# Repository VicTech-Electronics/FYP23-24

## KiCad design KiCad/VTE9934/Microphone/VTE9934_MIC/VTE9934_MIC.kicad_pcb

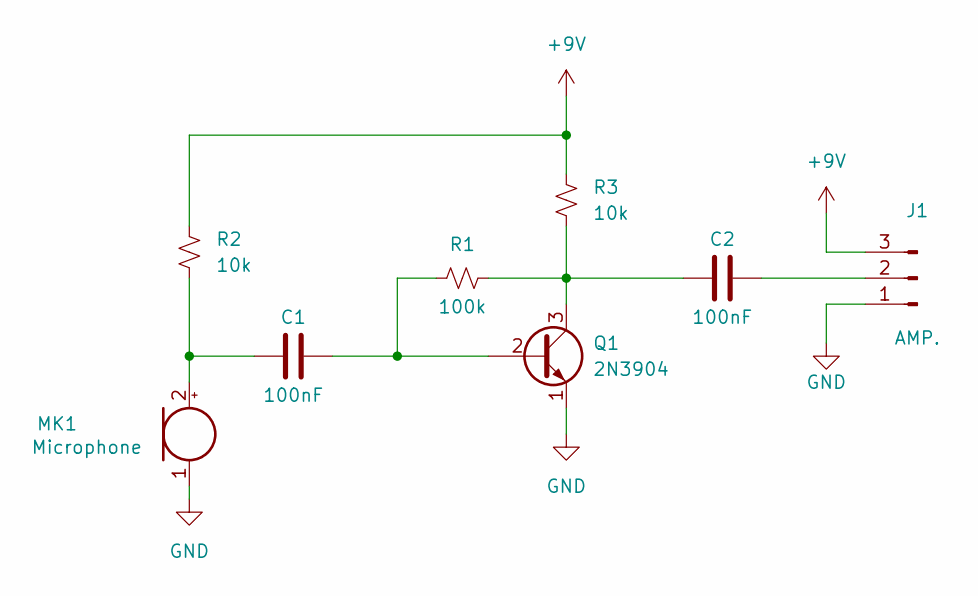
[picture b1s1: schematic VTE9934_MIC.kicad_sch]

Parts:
C1, C2: 100nF; C_Disc_D3.8mm_W2.6mm_P2.50mm
J1: AMP.; PinHeader_1x03_P2.54mm_Horizontal
MK1: Microphone; POM-2244P-C3310-2-R
Q1: 2N3904; TO-92_Inline
R1: 100k; R_Axial_DIN0207_L6.3mm_D2.5mm_P10.16mm_Horizontal
R2, R3: 10k; R_Axial_DIN0207_L6.3mm_D2.5mm_P10.16mm_Horizontal

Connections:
+9V: J1.3, R2.2, R3.2
GND: J1.1, MK1.1 (-), Q1.1 (E)
unnamed: C2.2, J1.2
unnamed: C1.1, MK1.2 (+), R2.1
unnamed: C1.2, Q1.2 (B), R1.1
unnamed: C2.1, Q1.3 (C), R1.2, R3.1

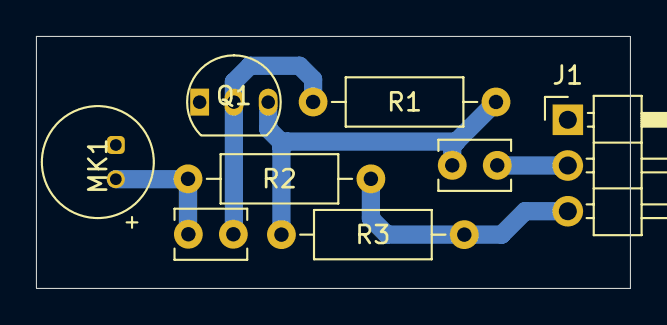
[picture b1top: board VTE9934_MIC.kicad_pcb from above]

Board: 2 copper layers, 33.0 x 14.0 mm, 8 parts (0 on the bottom side), 6 nets.

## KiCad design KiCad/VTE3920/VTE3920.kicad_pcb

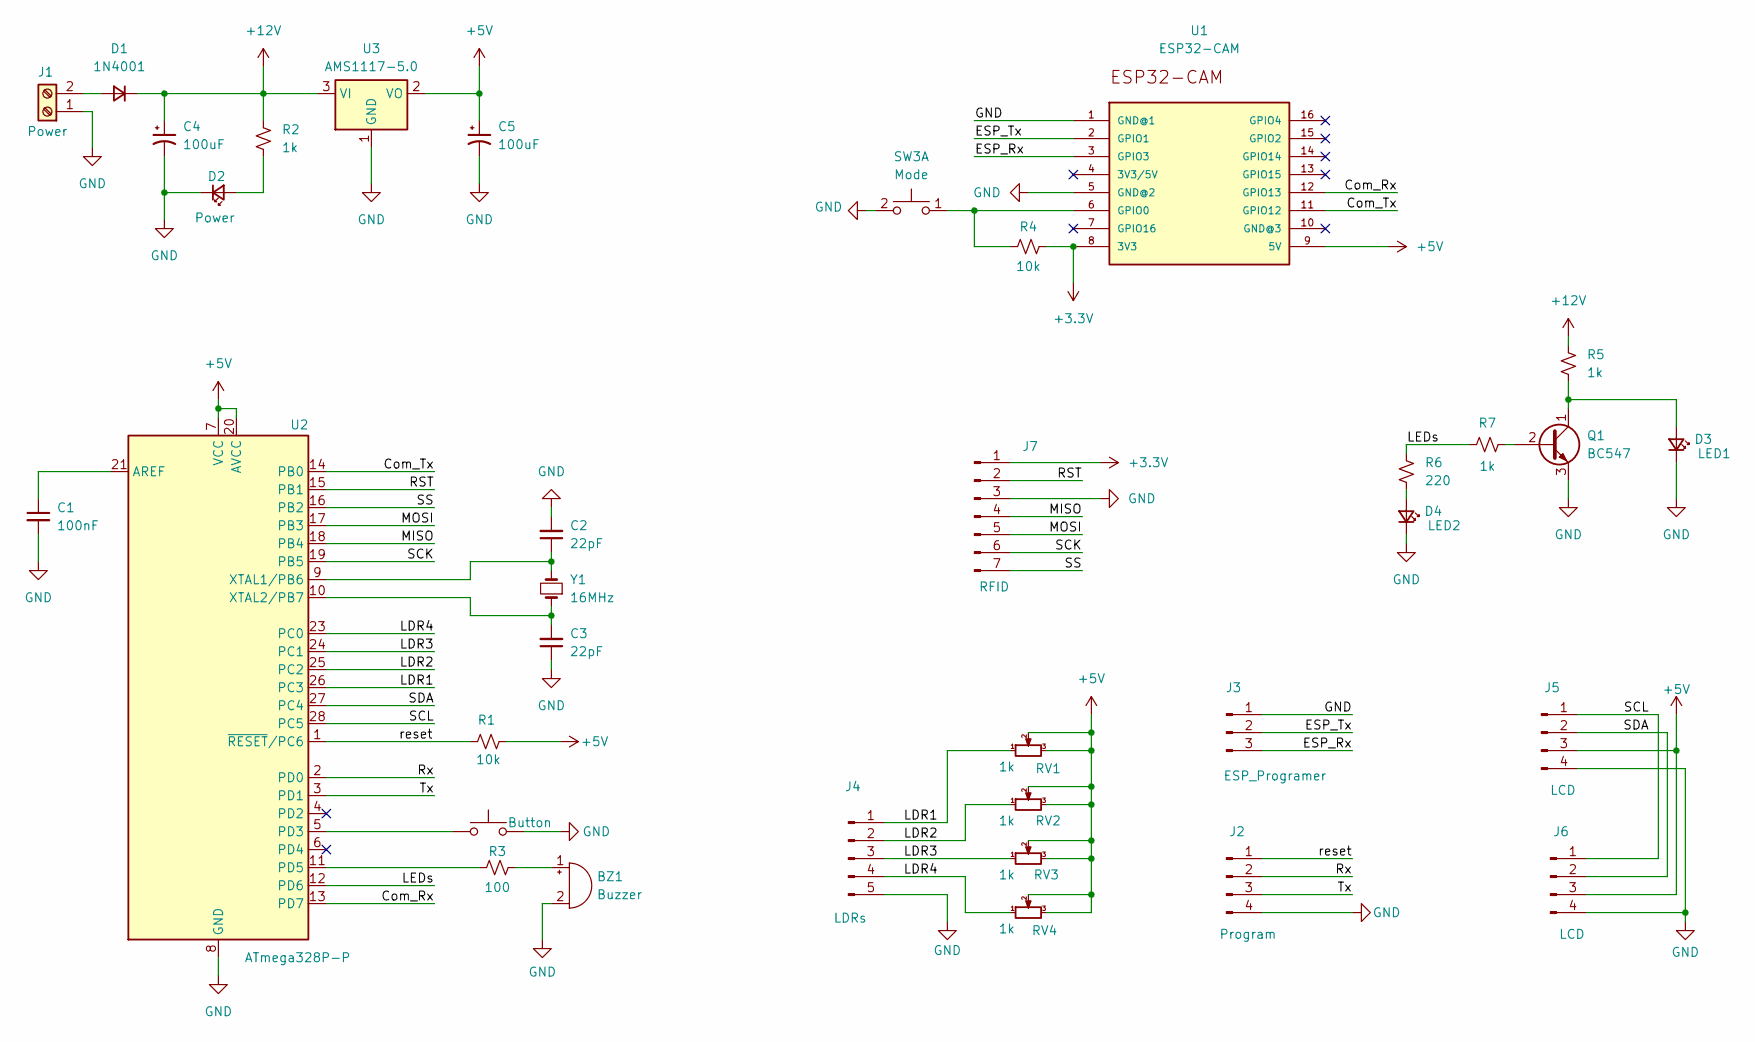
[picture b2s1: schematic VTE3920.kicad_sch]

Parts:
BZ1: Buzzer; Buzzer_12x9.5RM7.6
C1: 100nF; C_Disc_D3.0mm_W1.6mm_P2.50mm
C2, C3: 22pF; C_Disc_D3.0mm_W1.6mm_P2.50mm
C4, C5: 100uF; CP_Radial_D5.0mm_P2.50mm
D1: 1N4001; D_A-405_P10.16mm_Horizontal
D2: Power; LED_D3.0mm
D3: LED1; LED_D3.0mm
D4: LED2; LED_D3.0mm
J1: Power; TerminalBlock_bornier-2_P5.08mm
J2: Program; PinHeader_1x04_P2.54mm_Vertical
J3: ESP_Programer; PinHeader_1x03_P2.54mm_Vertical
J4: LDRs; PinHeader_1x05_P2.54mm_Vertical
J5, J6: LCD; PinHeader_1x04_P2.54mm_Vertical
J7: RFID; PinHeader_1x07_P2.54mm_Vertical
Q1: BC547; TO-92_Inline
R1, R4: 10k; R_Axial_DIN0207_L6.3mm_D2.5mm_P10.16mm_Horizontal
R2, R5, R7: 1k; R_Axial_DIN0207_L6.3mm_D2.5mm_P10.16mm_Horizontal
R3: 100; R_Axial_DIN0207_L6.3mm_D2.5mm_P10.16mm_Horizontal
R6: 220; R_Axial_DIN0207_L6.3mm_D2.5mm_P10.16mm_Horizontal
RV1, RV2, RV3, RV4: 1k; Potentiometer_Runtron_RM-065_Vertical
SW1: Button; TestPoint_2Pads_Pitch2.54mm_Drill0.8mm
SW3: Mode; SW_PUSH_6mm
U1: ESP32-CAM
U2: ATmega328P-P; DIP-28_W7.62mm_Socket_LongPads
U3: AMS1117-5.0; SOT-223-3_TabPin2
Y1: 16MHz; Crystal_HC50_Vertical

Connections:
+3.3V: J7.1, R4.2, U1.8 (3V3)
+5V: C5.1, J5.3, J6.3, R1.2, RV1.2, RV1.3, RV2.2, RV2.3, RV3.2, RV3.3, RV4.2, RV4.3, U1.9 (5V), U2.7 (VCC), U2.20 (AVCC), U3.2 (VO)
+12V: C4.1, D1.1 (K), R2.1, R5.1, U3.3 (VI)
/Com_Rx: U1.12 (GPIO13), U2.13 (PD7)
/Com_Tx: U1.11 (GPIO12), U2.14 (PB0)
/ESP_Rx: J3.3, U1.3 (GPIO3)
/ESP_Tx: J3.2, U1.2 (GPIO1)
/LDR1: J4.1, RV1.1, U2.26 (PC3)
/LDR2: J4.2, RV2.1, U2.25 (PC2)
/LDR3: J4.3, RV3.1, U2.24 (PC1)
/LDR4: J4.4, RV4.1, U2.23 (PC0)
/LEDs: R6.1, R7.1, U2.12 (PD6)
/MISO: J7.4, U2.18 (PB4)
/MOSI: J7.5, U2.17 (PB3)
/RST: J7.2, U2.15 (PB1)
/Rx: J2.2, U2.2 (PD0)
/SCK: J7.6, U2.19 (PB5)
/SCL: J5.1, J6.1, U2.28 (PC5)
/SDA: J5.2, J6.2, U2.27 (PC4)
/SS: J7.7, U2.16 (PB2)
/Tx: J2.3, U2.3 (PD1)
/reset: J2.1, R1.1, U2.1 (~RESET/PC6)
GND: BZ1.2 (-), C1.2, C2.2, C3.1, C4.2, C5.2, D2.1 (K), D3.1 (K), D4.1 (K), J1.1, J2.4, J3.1, J4.5, J5.4, J6.4, J7.3, Q1.3 (E), SW1.2, SW3.2 (D), U1.1 (GND@1), U1.5 (GND@2), U2.8 (GND), U2.22 (GND), U3.1 (GND)
unnamed: BZ1.1 (+), R3.2
unnamed: D1.2 (A), J1.2
unnamed: D2.2 (A), R2.2
unnamed: D3.2 (A), Q1.1 (C), R5.2
unnamed: D4.2 (A), R6.2
unnamed: Q1.2 (B), R7.2
unnamed: R4.1, SW3.1 (C), U1.6 (GPIO0)
unnamed: C1.1, U2.21 (AREF)
unnamed: SW1.1, U2.5 (PD3)
unnamed: R3.1, U2.11 (PD5)
unnamed: C2.1, U2.9 (XTAL1/PB6), Y1.2
unnamed: C3.2, U2.10 (XTAL2/PB7), Y1.1

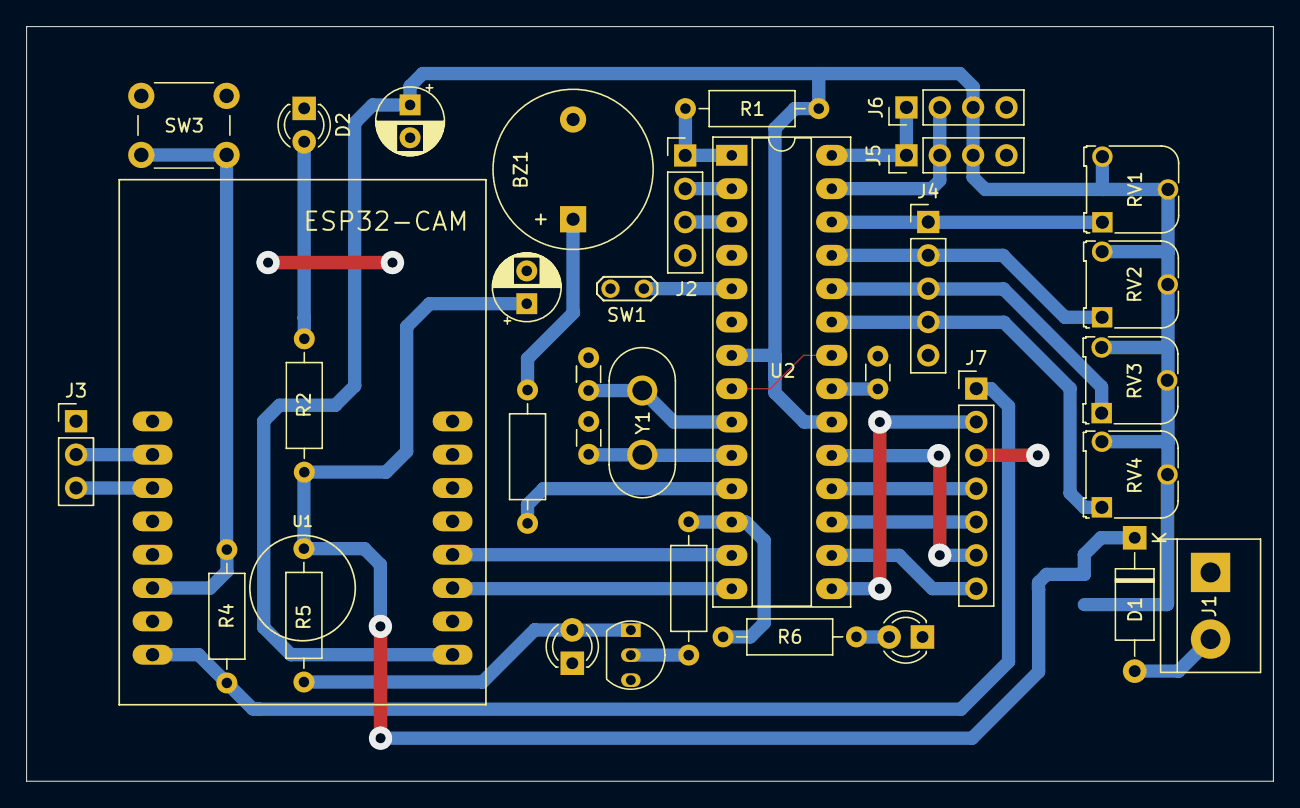
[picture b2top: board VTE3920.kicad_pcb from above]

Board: 2 copper layers, 95.0 x 57.5 mm, 35 parts (1 on the bottom side), 35 nets.

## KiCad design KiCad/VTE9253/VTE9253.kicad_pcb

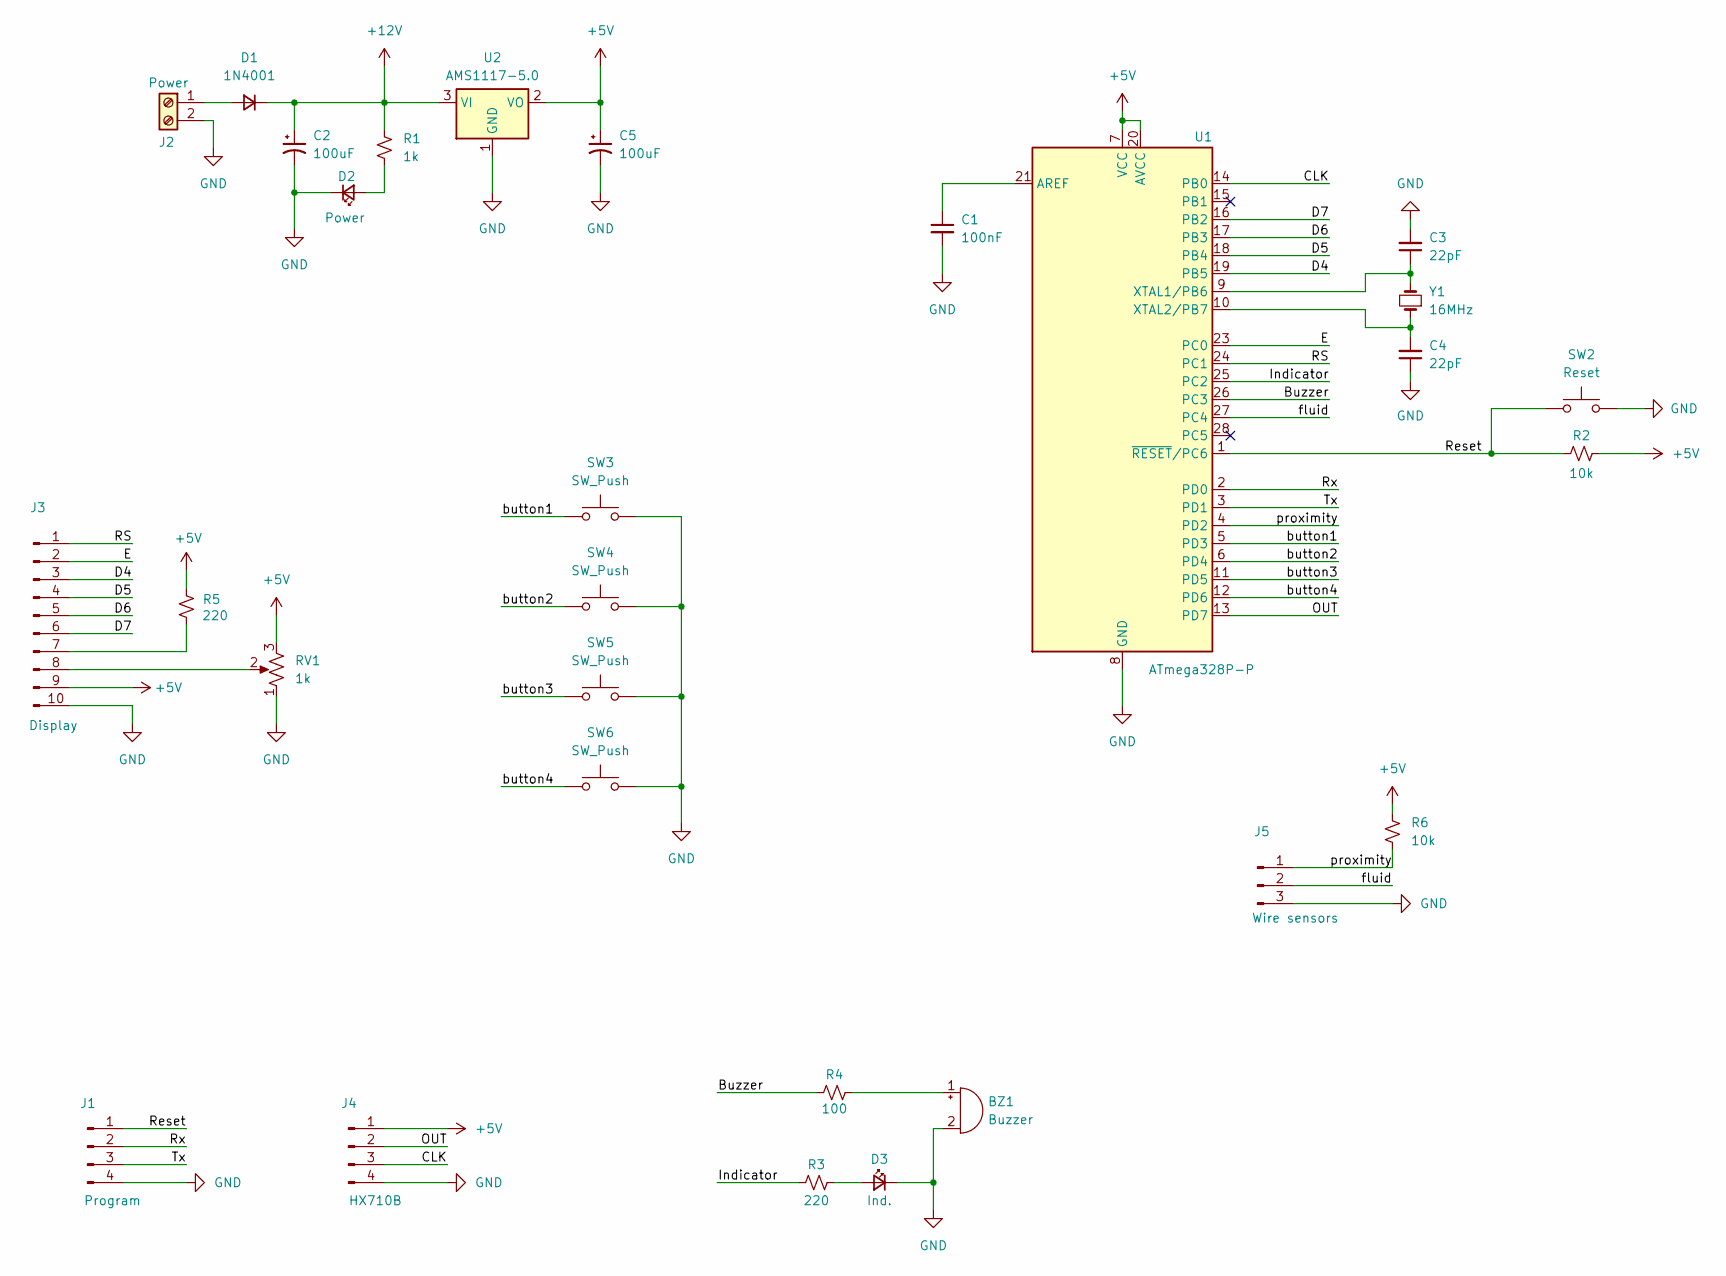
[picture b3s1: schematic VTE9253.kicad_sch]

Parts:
BZ1: Buzzer; Buzzer_12x9.5RM7.6
C1: 100nF; C_Disc_D3.0mm_W1.6mm_P2.50mm
C2, C5: 100uF; CP_Radial_D5.0mm_P2.50mm
C3, C4: 22pF; C_Disc_D3.0mm_W1.6mm_P2.50mm
D1: 1N4001; D_A-405_P10.16mm_Horizontal
D2: Power; LED_D3.0mm
D3: Ind.; LED_D3.0mm
J1: Program; PinHeader_1x04_P2.54mm_Vertical
J2: Power; TerminalBlock_bornier-2_P5.08mm
J3: Display; PinHeader_1x10_P2.54mm_Vertical
J4: HX710B; PinHeader_1x04_P2.54mm_Vertical
J5: Wire sensors; PinHeader_1x03_P2.54mm_Vertical
R1: 1k; R_Axial_DIN0207_L6.3mm_D2.5mm_P10.16mm_Horizontal
R2, R6: 10k; R_Axial_DIN0207_L6.3mm_D2.5mm_P10.16mm_Horizontal
R3, R5: 220; R_Axial_DIN0207_L6.3mm_D2.5mm_P10.16mm_Horizontal
R4: 100; R_Axial_DIN0207_L6.3mm_D2.5mm_P10.16mm_Horizontal
RV1: 1k; Potentiometer_Runtron_RM-065_Vertical
SW2: Reset; SW_PUSH_6mm
SW3, SW4, SW5, SW6: SW_Push; TestPoint_2Pads_Pitch2.54mm_Drill0.8mm
U1: ATmega328P-P; DIP-28_W7.62mm_Socket_LongPads
U2: AMS1117-5.0; SOT-223-3_TabPin2
Y1: 16MHz; Crystal_HC50_Vertical

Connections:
+5V: C5.1, J3.9, J4.1, R2.2, R5.2, R6.1, RV1.3, U1.7 (VCC), U1.20 (AVCC), U2.2 (VO)
+12V: C2.1, D1.1 (K), R1.1, U2.3 (VI)
/Buzzer: R4.1, U1.26 (PC3)
/CLK: J4.3, U1.14 (PB0)
/D4: J3.3, U1.19 (PB5)
/D5: J3.4, U1.18 (PB4)
/D6: J3.5, U1.17 (PB3)
/D7: J3.6, U1.16 (PB2)
/E: J3.2, U1.23 (PC0)
/Indicator: R3.1, U1.25 (PC2)
/OUT: J4.2, U1.13 (PD7)
/RS: J3.1, U1.24 (PC1)
/Reset: J1.1, R2.1, SW2.1, U1.1 (~RESET/PC6)
/Rx: J1.2, U1.2 (PD0)
/Tx: J1.3, U1.3 (PD1)
/button1: SW3.2, U1.5 (PD3)
/button2: SW4.2, U1.6 (PD4)
/button3: SW5.2, U1.11 (PD5)
/button4: SW6.2, U1.12 (PD6)
/fluid: J5.2, U1.27 (PC4)
/proximity: J5.1, R6.2, U1.4 (PD2)
GND: BZ1.2 (-), C1.2, C2.2, C3.2, C4.1, C5.2, D2.1 (K), D3.1 (K), J1.4, J2.2, J3.10, J4.4, J5.3, RV1.1, SW2.2, SW3.1, SW4.1, SW5.1, SW6.1, U1.8 (GND), U1.22 (GND), U2.1 (GND)
unnamed: BZ1.1 (+), R4.2
unnamed: D1.2 (A), J2.1
unnamed: D2.2 (A), R1.2
unnamed: D3.2 (A), R3.2
unnamed: J3.7, R5.1
unnamed: J3.8, RV1.2
unnamed: C1.1, U1.21 (AREF)
unnamed: C3.1, U1.9 (XTAL1/PB6), Y1.2
unnamed: C4.2, U1.10 (XTAL2/PB7), Y1.1

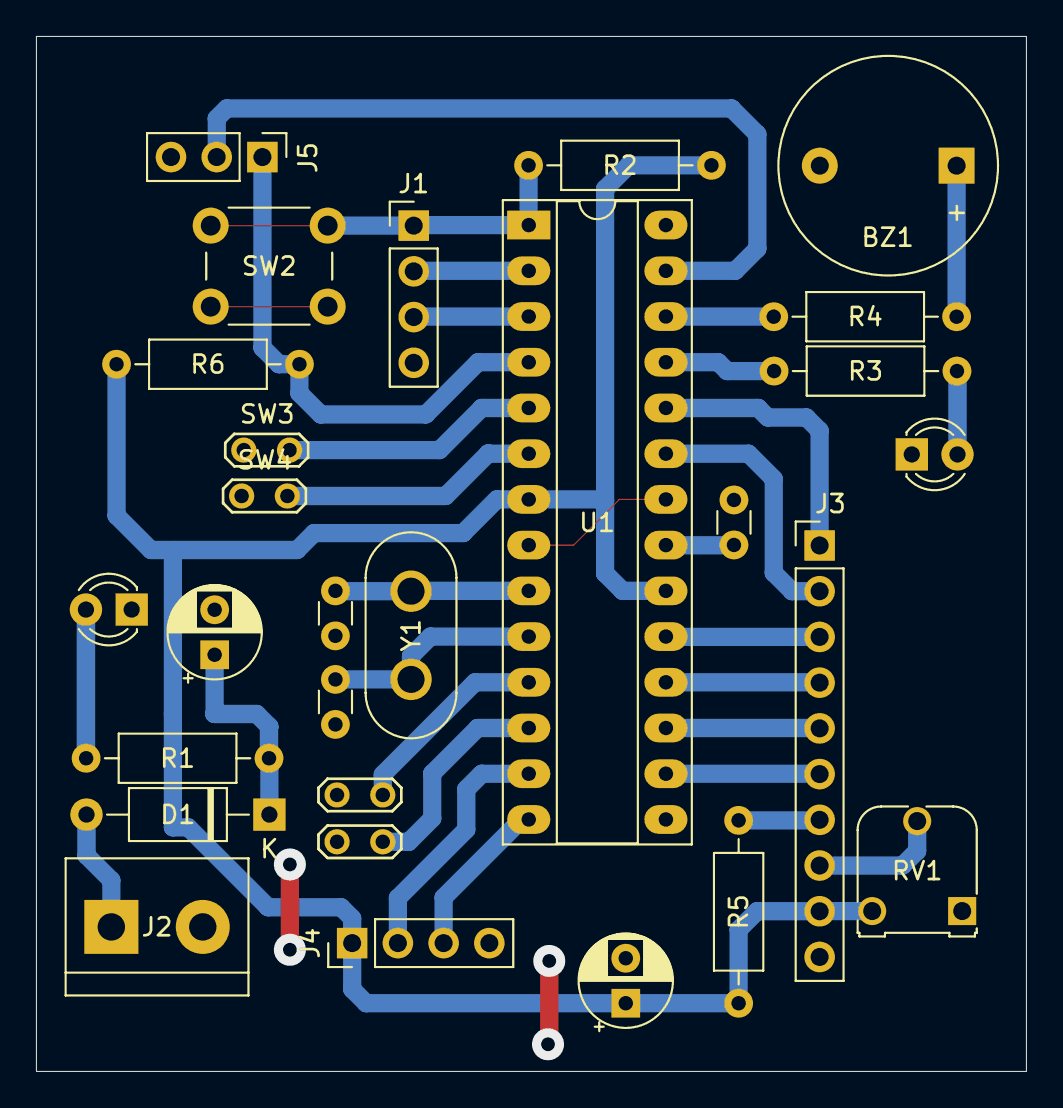
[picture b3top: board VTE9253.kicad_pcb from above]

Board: 2 copper layers, 55.0 x 57.5 mm, 29 parts (1 on the bottom side), 31 nets.

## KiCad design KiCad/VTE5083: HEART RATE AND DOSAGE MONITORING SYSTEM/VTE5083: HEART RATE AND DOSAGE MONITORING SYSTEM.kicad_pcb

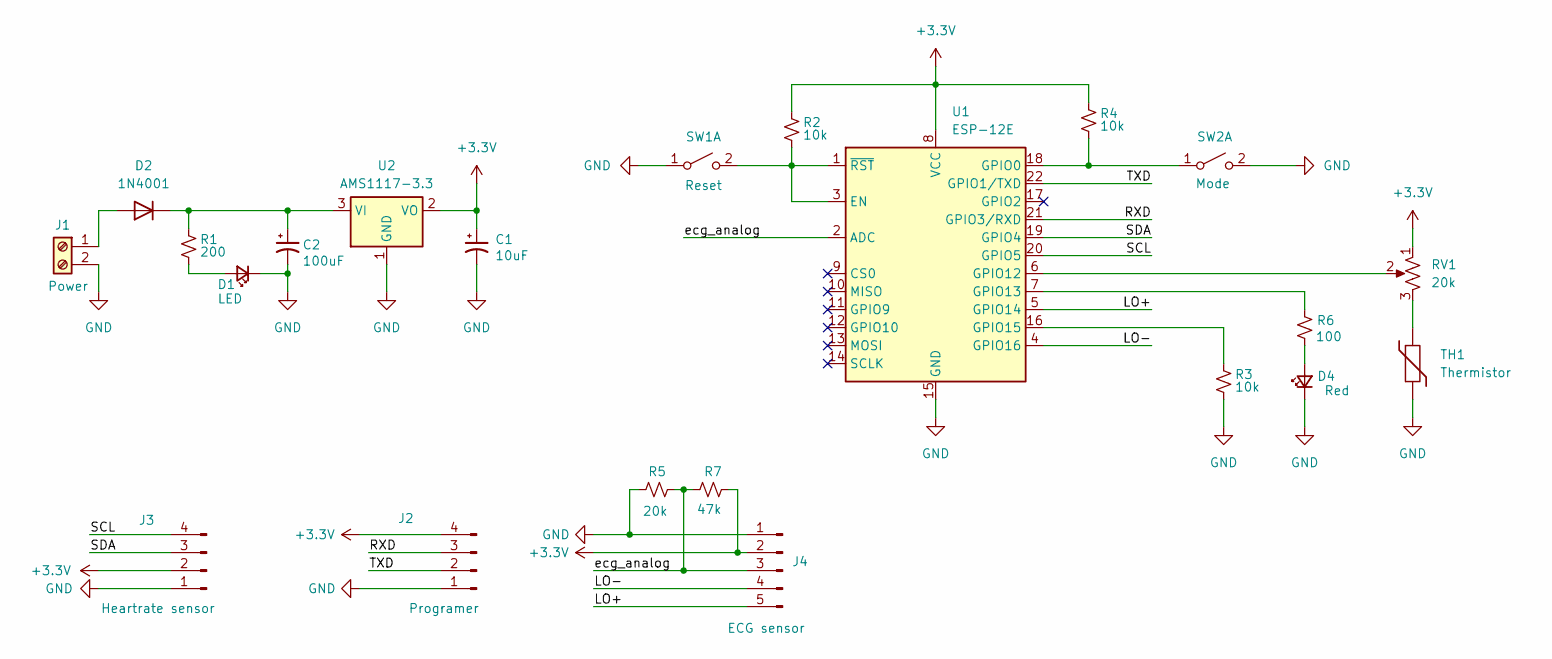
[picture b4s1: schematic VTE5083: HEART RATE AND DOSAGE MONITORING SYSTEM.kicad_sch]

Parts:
C1: 10uF; CP_Radial_D4.0mm_P2.00mm
C2: 100uF; CP_Radial_D4.0mm_P2.00mm
D1: LED; LED_D3.0mm_Clear
D2: 1N4001; D_DO-41_SOD81_P10.16mm_Horizontal
D4: Red; LED_D3.0mm_Clear
J1: Power; TerminalBlock_bornier-2_P5.08mm
J2: Programer; PinHeader_1x04_P2.54mm_Vertical
J3: Heartrate sensor; PinHeader_1x04_P2.54mm_Vertical
J4: ECG sensor; PinHeader_1x05_P2.54mm_Vertical
R1: 200; R_Axial_DIN0207_L6.3mm_D2.5mm_P10.16mm_Horizontal
R2, R3, R4: 10k; R_Axial_DIN0207_L6.3mm_D2.5mm_P10.16mm_Horizontal
R5: 20k; R_Axial_DIN0207_L6.3mm_D2.5mm_P10.16mm_Horizontal
R6: 100; R_Axial_DIN0207_L6.3mm_D2.5mm_P10.16mm_Horizontal
R7: 47k; R_Axial_DIN0207_L6.3mm_D2.5mm_P10.16mm_Horizontal
RV1: 20k; Potentiometer_Runtron_RM-065_Vertical
SW1: Reset; SW_PUSH_6mm
SW2: Mode; SW_PUSH_6mm
TH1: Thermistor; Osram_SFH225
U1: ESP-12E
U2: AMS1117-3.3; SOT-223-3_TabPin2

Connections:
+3.3V: C1.1, J2.4, J3.2, J4.2, R2.1, R4.1, R7.1, RV1.1, U1.8 (VCC), U2.2 (VO)
/LO+: J4.5, U1.5 (GPIO14)
/LO-: J4.4, U1.4 (GPIO16)
/RXD: J2.3, U1.21 (GPIO3/RXD)
/SCL: J3.4, U1.20 (GPIO5)
/SDA: J3.3, U1.19 (GPIO4)
/TXD: J2.2, U1.22 (GPIO1/TXD)
/ecg_analog: J4.3, R5.1, R7.2, U1.2 (ADC)
GND: C1.2, C2.2, D1.1 (K), D4.1 (K), J1.2, J2.1, J3.1, J4.1, R3.2, R5.2, SW1.1 (A), SW2.2 (B), TH1.2, U1.15 (GND), U2.1 (GND)
unnamed: D1.2 (A), R1.2
unnamed: D2.2 (A), J1.1
unnamed: C2.1, D2.1 (K), R1.1, U2.3 (VI)
unnamed: D4.2 (A), R6.1
unnamed: RV1.3, TH1.1
unnamed: R2.2, SW1.2 (B), U1.1 (~RST), U1.3 (EN)
unnamed: R4.2, SW2.1 (A), U1.18 (GPIO0)
unnamed: RV1.2, U1.6 (GPIO12)
unnamed: R6.2, U1.7 (GPIO13)
unnamed: R3.1, U1.16 (GPIO15)

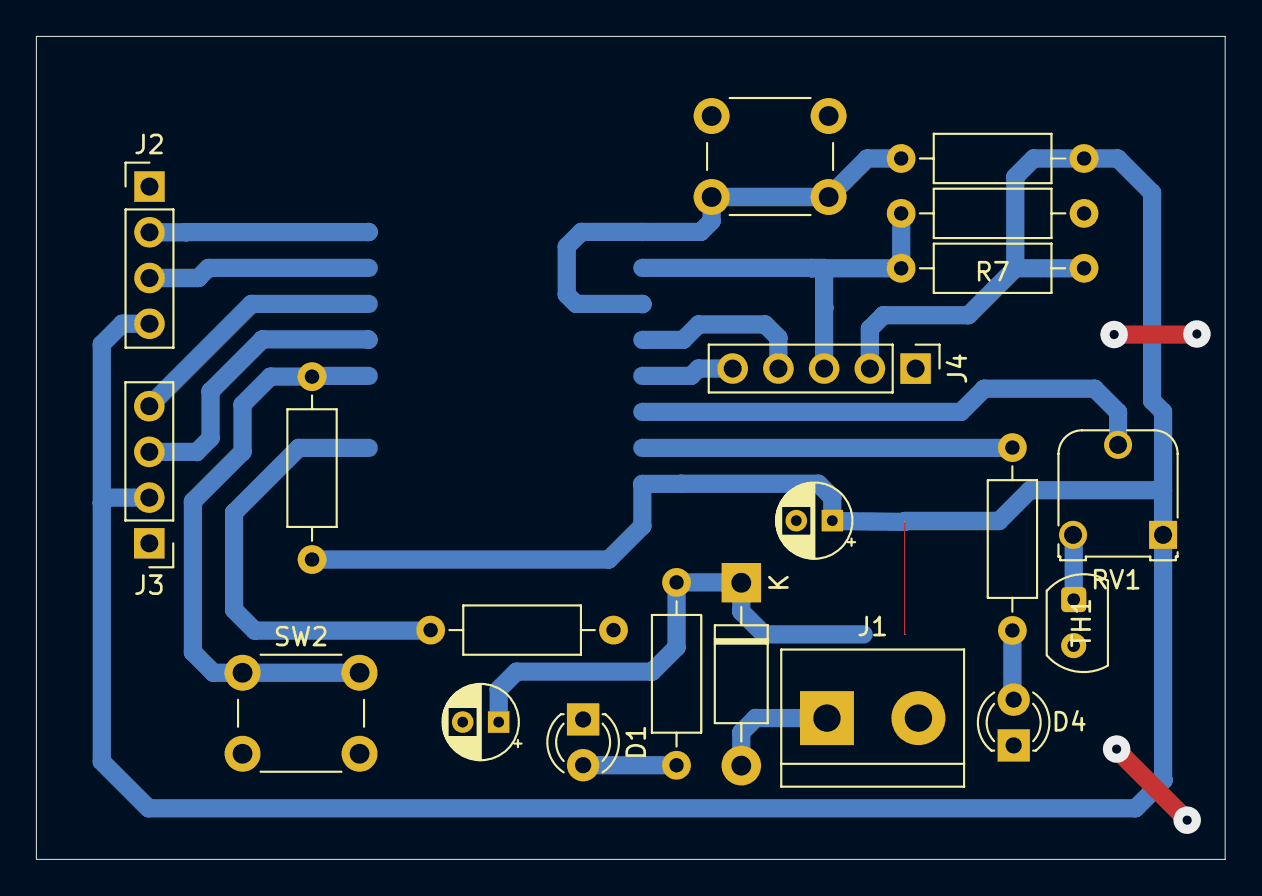
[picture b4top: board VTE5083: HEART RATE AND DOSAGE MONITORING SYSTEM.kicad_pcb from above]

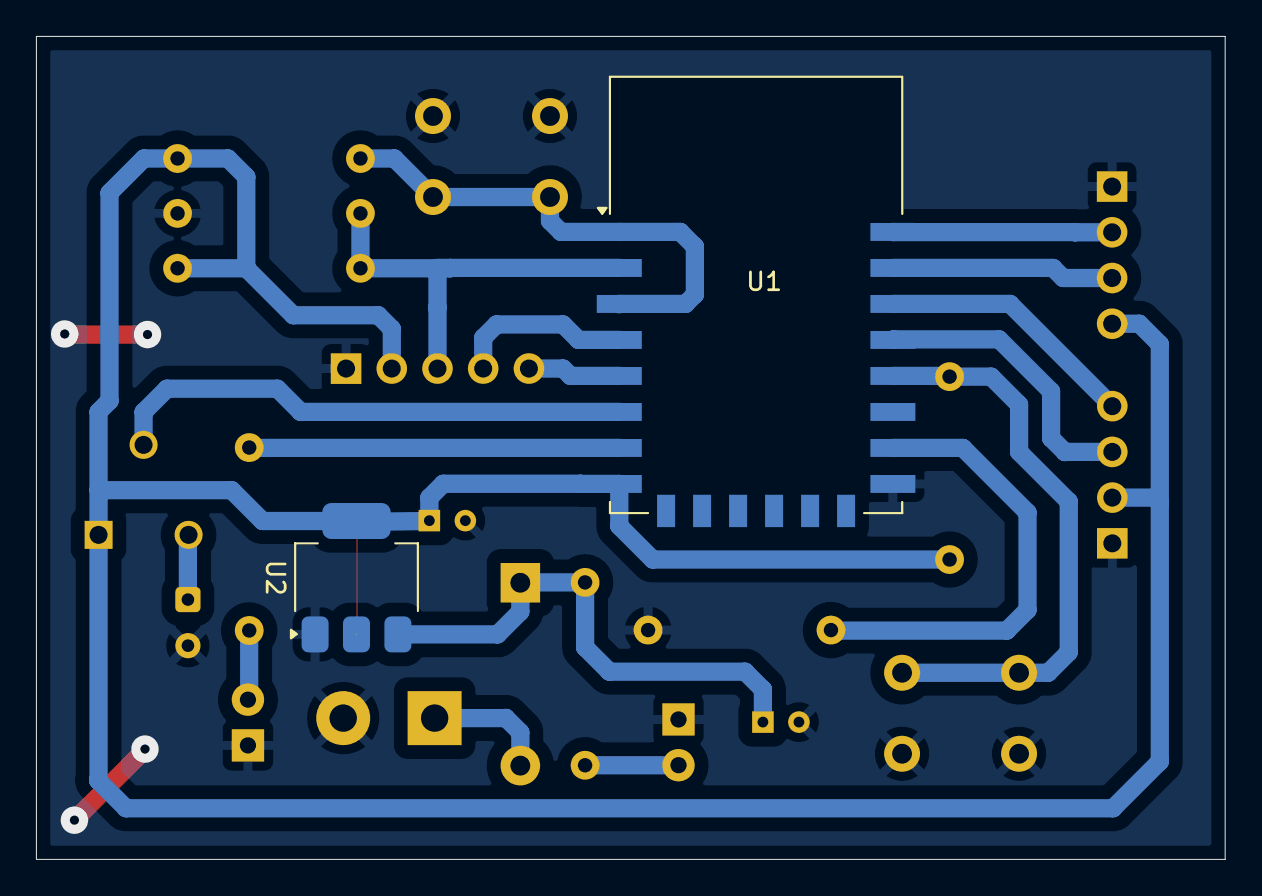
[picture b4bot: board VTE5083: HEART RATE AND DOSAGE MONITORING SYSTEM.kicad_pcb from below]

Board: 2 copper layers, 66.0 x 45.7 mm, 22 parts (2 on the bottom side), 19 nets.

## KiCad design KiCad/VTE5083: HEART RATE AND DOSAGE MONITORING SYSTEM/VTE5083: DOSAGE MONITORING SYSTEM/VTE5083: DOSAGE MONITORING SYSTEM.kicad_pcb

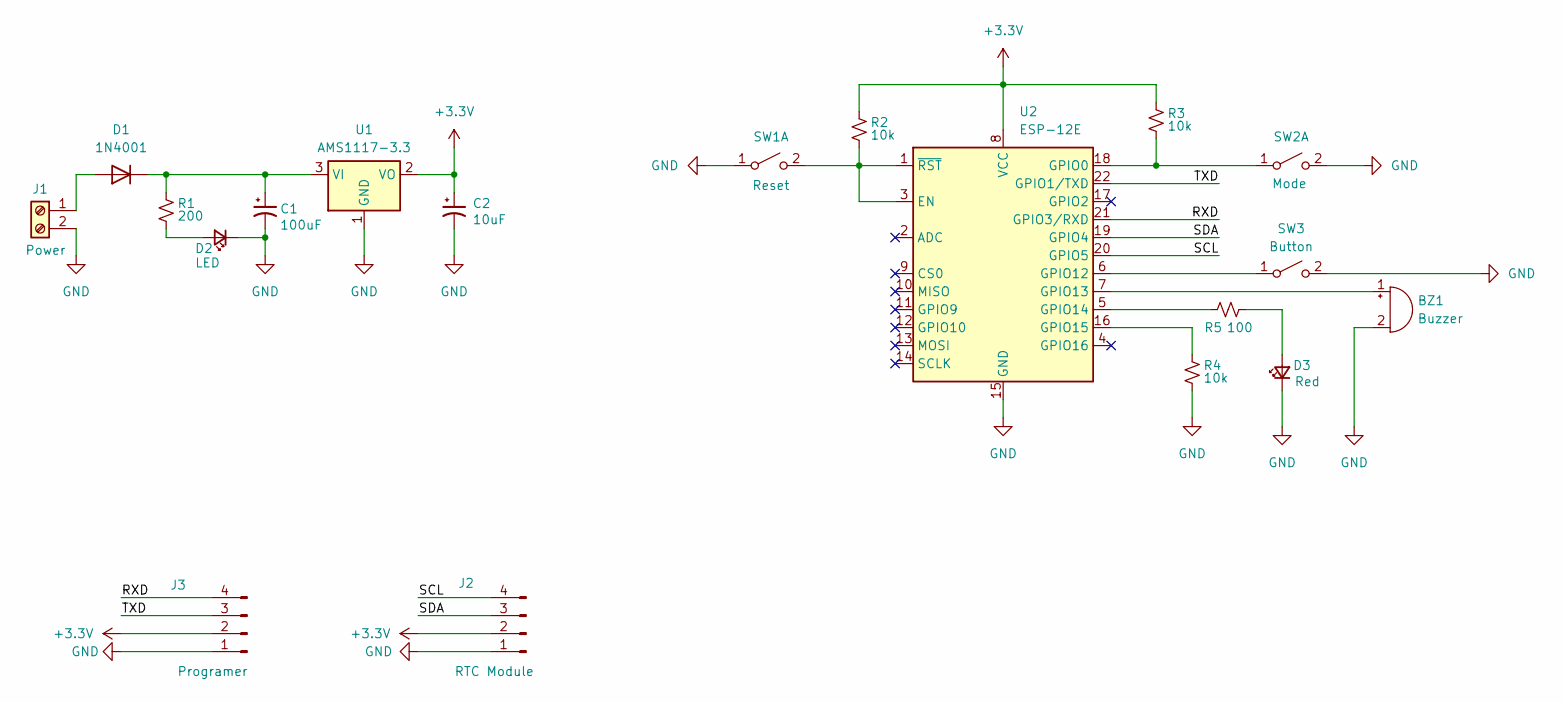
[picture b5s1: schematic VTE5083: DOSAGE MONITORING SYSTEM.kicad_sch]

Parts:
BZ1: Buzzer; Buzzer_15x7.5RM7.6
C1: 100uF; CP_Radial_D4.0mm_P2.00mm
C2: 10uF; CP_Radial_D4.0mm_P2.00mm
D1: 1N4001; D_DO-41_SOD81_P10.16mm_Horizontal
D2: LED; LED_D3.0mm_Clear
D3: Red; LED_D3.0mm_Clear
J1: Power; TerminalBlock_bornier-2_P5.08mm
J2: RTC Module; PinHeader_1x04_P2.54mm_Vertical
J3: Programer; PinHeader_1x04_P2.54mm_Vertical
R1: 200; R_Axial_DIN0207_L6.3mm_D2.5mm_P10.16mm_Horizontal
R2, R3, R4: 10k; R_Axial_DIN0207_L6.3mm_D2.5mm_P10.16mm_Horizontal
R5: 100; R_Axial_DIN0207_L6.3mm_D2.5mm_P10.16mm_Horizontal
SW1: Reset; SW_PUSH_6mm
SW2: Mode; SW_PUSH_6mm
SW3: Button; PinHeader_1x02_P2.54mm_Vertical
U1: AMS1117-3.3; SOT-223-3_TabPin2
U2: ESP-12E

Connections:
+3.3V: C2.1, J2.2, J3.2, R2.1, R3.1, U1.2 (VO), U2.8 (VCC)
/RXD: J3.4, U2.21 (GPIO3/RXD)
/SCL: J2.4, U2.20 (GPIO5)
/SDA: J2.3, U2.19 (GPIO4)
/TXD: J3.3, U2.22 (GPIO1/TXD)
GND: BZ1.2 (-), C1.2, C2.2, D2.1 (K), D3.1 (K), J1.2, J2.1, J3.1, R4.2, SW1.1 (A), SW2.2 (B), SW3.2 (B), U1.1 (GND), U2.15 (GND)
unnamed: BZ1.1 (+), U2.7 (GPIO13)
unnamed: D1.2 (A), J1.1
unnamed: C1.1, D1.1 (K), R1.1, U1.3 (VI)
unnamed: D2.2 (A), R1.2
unnamed: D3.2 (A), R5.2
unnamed: R2.2, SW1.2 (B), U2.1 (~RST), U2.3 (EN)
unnamed: R3.2, SW2.1 (A), U2.18 (GPIO0)
unnamed: SW3.1 (A), U2.6 (GPIO12)
unnamed: R5.1, U2.5 (GPIO14)
unnamed: R4.1, U2.16 (GPIO15)

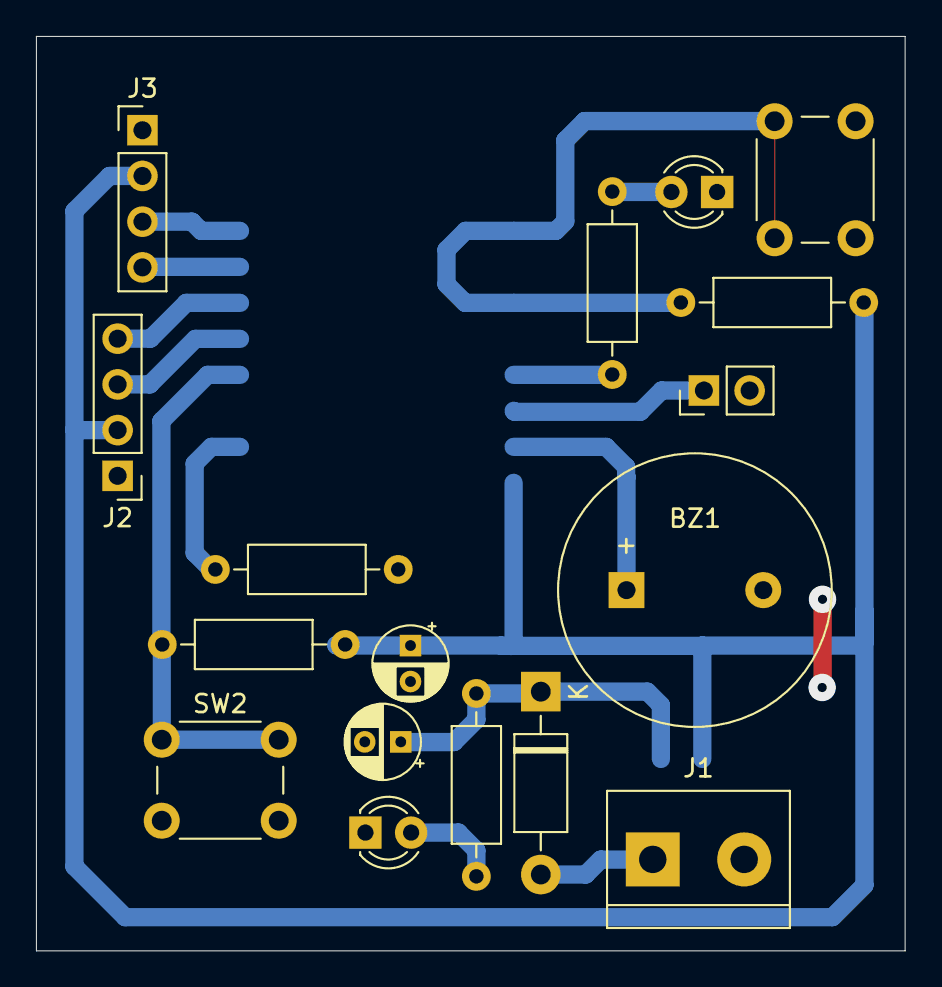
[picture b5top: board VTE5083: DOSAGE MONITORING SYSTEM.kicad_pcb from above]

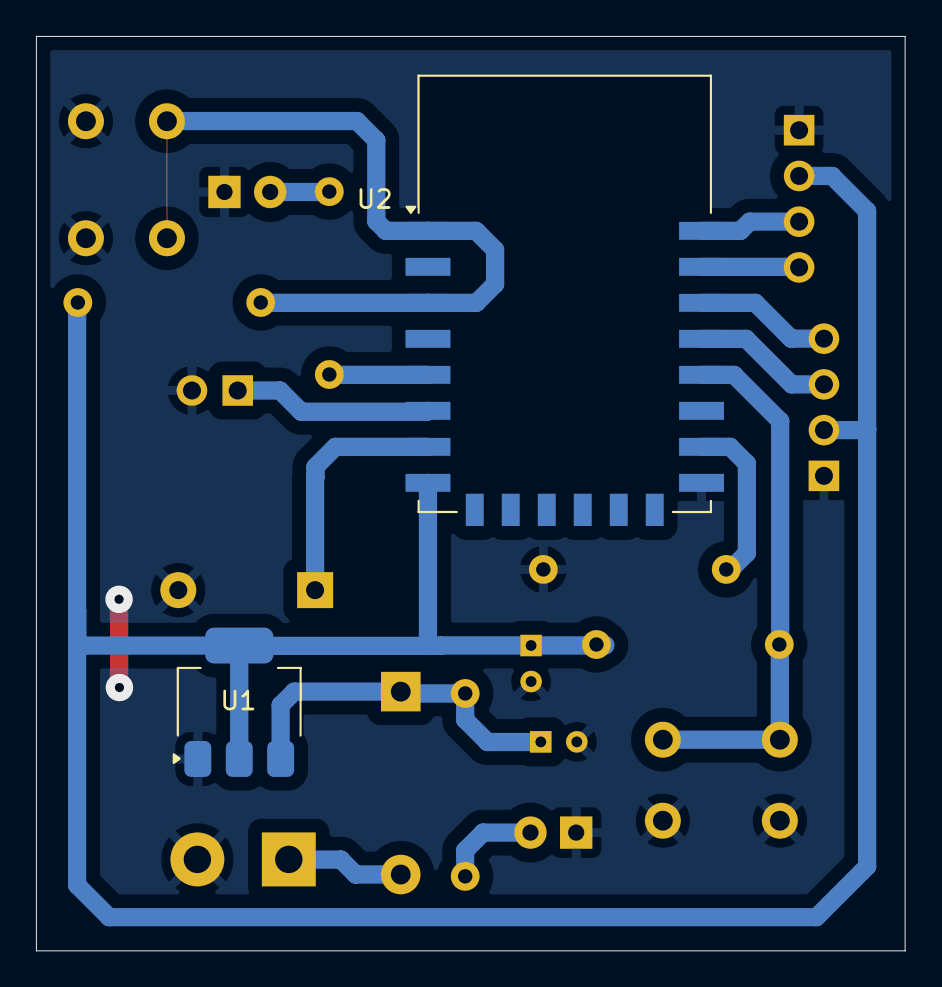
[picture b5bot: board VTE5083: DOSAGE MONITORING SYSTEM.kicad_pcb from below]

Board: 2 copper layers, 48.3 x 50.8 mm, 19 parts (2 on the bottom side), 16 nets.

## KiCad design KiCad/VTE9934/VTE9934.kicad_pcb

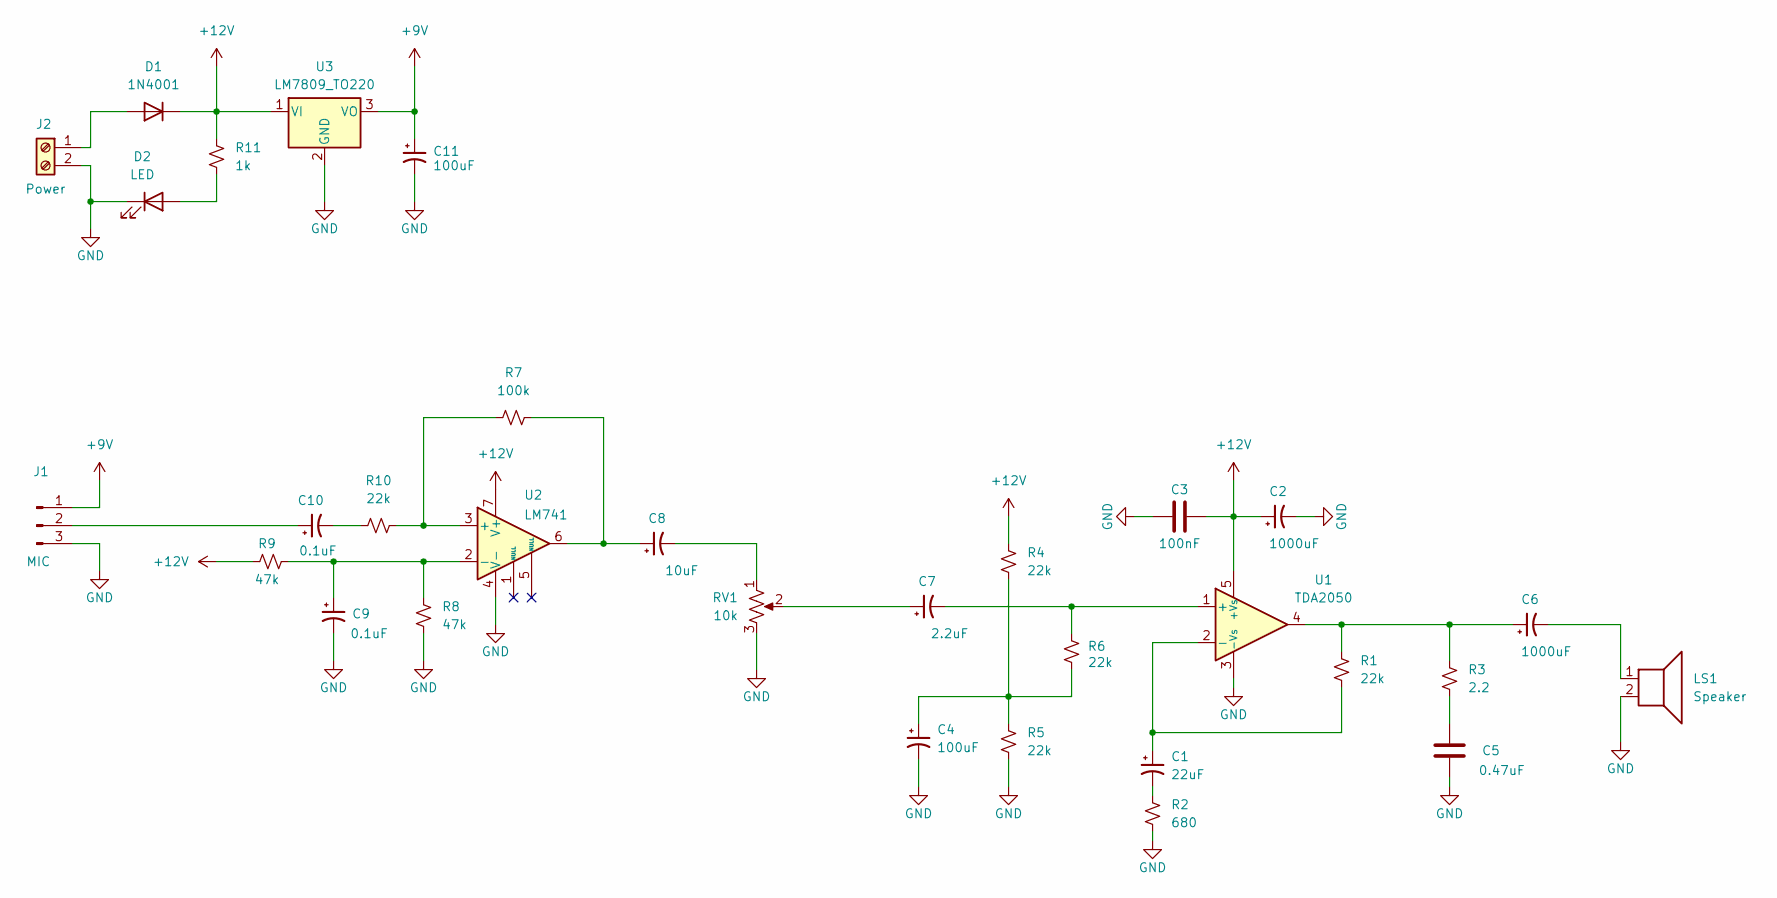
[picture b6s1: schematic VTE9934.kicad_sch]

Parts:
C1: 22uF; CP_Radial_D5.0mm_P2.50mm
C2: 1000uF; CP_Radial_D6.3mm_P2.50mm
C3: 100nF; C_Disc_D3.8mm_W2.6mm_P2.50mm
C4, C11: 100uF; CP_Radial_D5.0mm_P2.50mm
C5: 0.47uF; C_Disc_D3.8mm_W2.6mm_P2.50mm
C6: 1000uF; CP_Radial_D5.0mm_P2.50mm
C7: 2.2uF; CP_Radial_D5.0mm_P2.50mm
C8: 10uF; CP_Radial_D5.0mm_P2.50mm
C9, C10: 0.1uF; CP_Radial_D5.0mm_P2.50mm
D1: 1N4001; D_DO-41_SOD81_P10.16mm_Horizontal
D2: LED; LED_D3.0mm_Clear
J1: MIC; PinHeader_1x03_P2.54mm_Horizontal
J2: Power; TerminalBlock_bornier-2_P5.08mm
LS1: Speaker; TerminalBlock_bornier-2_P5.08mm
R1, R4, R5, R6, R10: 22k; R_Axial_DIN0207_L6.3mm_D2.5mm_P10.16mm_Horizontal
R2: 680; R_Axial_DIN0207_L6.3mm_D2.5mm_P10.16mm_Horizontal
R3: 2.2; R_Axial_DIN0207_L6.3mm_D2.5mm_P10.16mm_Horizontal
R7: 100k; R_Axial_DIN0207_L6.3mm_D2.5mm_P10.16mm_Horizontal
R8, R9: 47k; R_Axial_DIN0207_L6.3mm_D2.5mm_P10.16mm_Horizontal
R11: 1k; R_Axial_DIN0207_L6.3mm_D2.5mm_P10.16mm_Horizontal
RV1: 10k; Potentiometer_Alps_RK09Y11_Single_Horizontal
U1: TDA2050; TO-220-5_P3.4x3.7mm_StaggerOdd_Lead3.8mm_Vertical
U2: LM741; DIP-8_W7.62mm_LongPads
U3: LM7809_TO220; TO-220-3_Vertical

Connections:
+9V: C11.1, J1.1, U3.3 (VO)
+12V: C2.1, C3.2, D1.1 (K), R4.1, R9.1, R11.2, U1.5 (+Vs), U2.7 (V+), U3.1 (VI)
GND: C2.2, C3.1, C4.2, C5.2, C9.2, C11.2, D2.1 (K), J1.3, J2.2, LS1.2, R2.2, R5.2, R8.2, RV1.3, U1.3 (-Vs), U2.4 (V-), U3.2 (GND)
unnamed: C1.2, R2.1
unnamed: C4.1, R4.2, R5.1, R6.1
unnamed: C5.1, R3.2
unnamed: C6.1, R1.1, R3.1, U1.4
unnamed: C6.2, LS1.1
unnamed: C7.1, RV1.2
unnamed: C8.1, R7.2, U2.6
unnamed: C8.2, RV1.1
unnamed: C10.2, R10.1
unnamed: D1.2 (A), J2.1
unnamed: D2.2 (A), R11.1
unnamed: C10.1, J1.2
unnamed: C7.2, R6.2, U1.1 (+)
unnamed: C1.1, R1.2, U1.2 (-)
unnamed: R7.1, R10.2, U2.3 (+)
unnamed: C9.1, R8.1, R9.2, U2.2 (-)

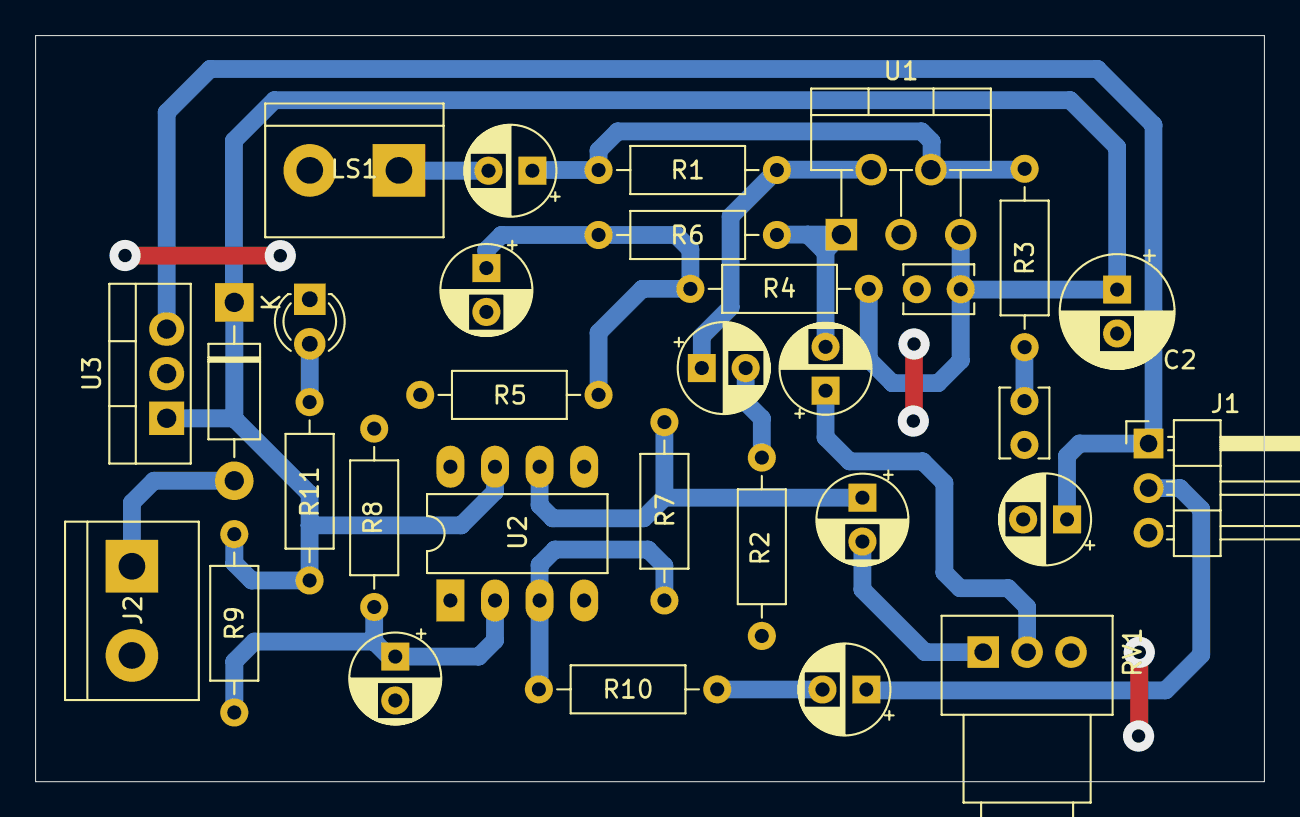
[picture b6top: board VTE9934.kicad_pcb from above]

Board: 2 copper layers, 70.0 x 42.5 mm, 31 parts (0 on the bottom side), 19 nets.
